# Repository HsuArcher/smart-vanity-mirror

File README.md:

# smart-vanity-mirror

Custom built ESP8266 based smart vanity mirror with touch controls, USB-C power and programming integration, custom CADed frame and custom PCB.

## Features

- Adustable LEDs brightness and color
- Touch Sensor Controls
- Custom Built Housing
- USB C Port for Power and Programming

## Hardware Overview

What this shows:
USB-C Programmer and Power Supply, Voltage Regulation, ESP8266 Microcontroller, Touch Input Circuit, LED Output Stage

### USB-C and USB to Serial Port

The system is powered and programmed through a USB-C connector supplying 5 V and a CH340C USB to Serial UART converter.

Key design elements:
- VBUS provides 5 V input.
- CC resistors are used to negotiate default USB power mode.
- The CH340C communicates with the ESP8266 when the USB C is connected to a computer. 
- GPIO 0 boot mode circuitry and Reset circuitry
- A polyfuse is used as overcurrent protection.

### Voltage Regulation

The ESP8266 operates at 3.3 V, so a voltage regulator steps down 5 V from USB-C to 3.3 V.

Key design elements:
- 5V to 3.3V Buck Converter

### ESP8266 Microcontroller

The ESP8266 serves as the main controller for, handling touch input, driving LED outputs, and managing firmware logic

Key design elements:
- Proper decoupling capacitors near VCC
- EN (enable) pull-up resistor
- Manual Reset Switch

### Touch Input Circuit

The FDC1004-Q1 is a 4-Channel Capacitance-to-Digital Converter which is used to detect when the user touches metal pads. This data is sent to the ESP8266 to control the lights

<!-- Future Improvements

Facial recognition lighting presets

Mobile app control

Ambient light auto-adjustment

Bluetooth speaker integration -->

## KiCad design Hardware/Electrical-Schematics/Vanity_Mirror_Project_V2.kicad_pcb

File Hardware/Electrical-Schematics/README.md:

# Schematics
KiCAD schematics files and PDFs

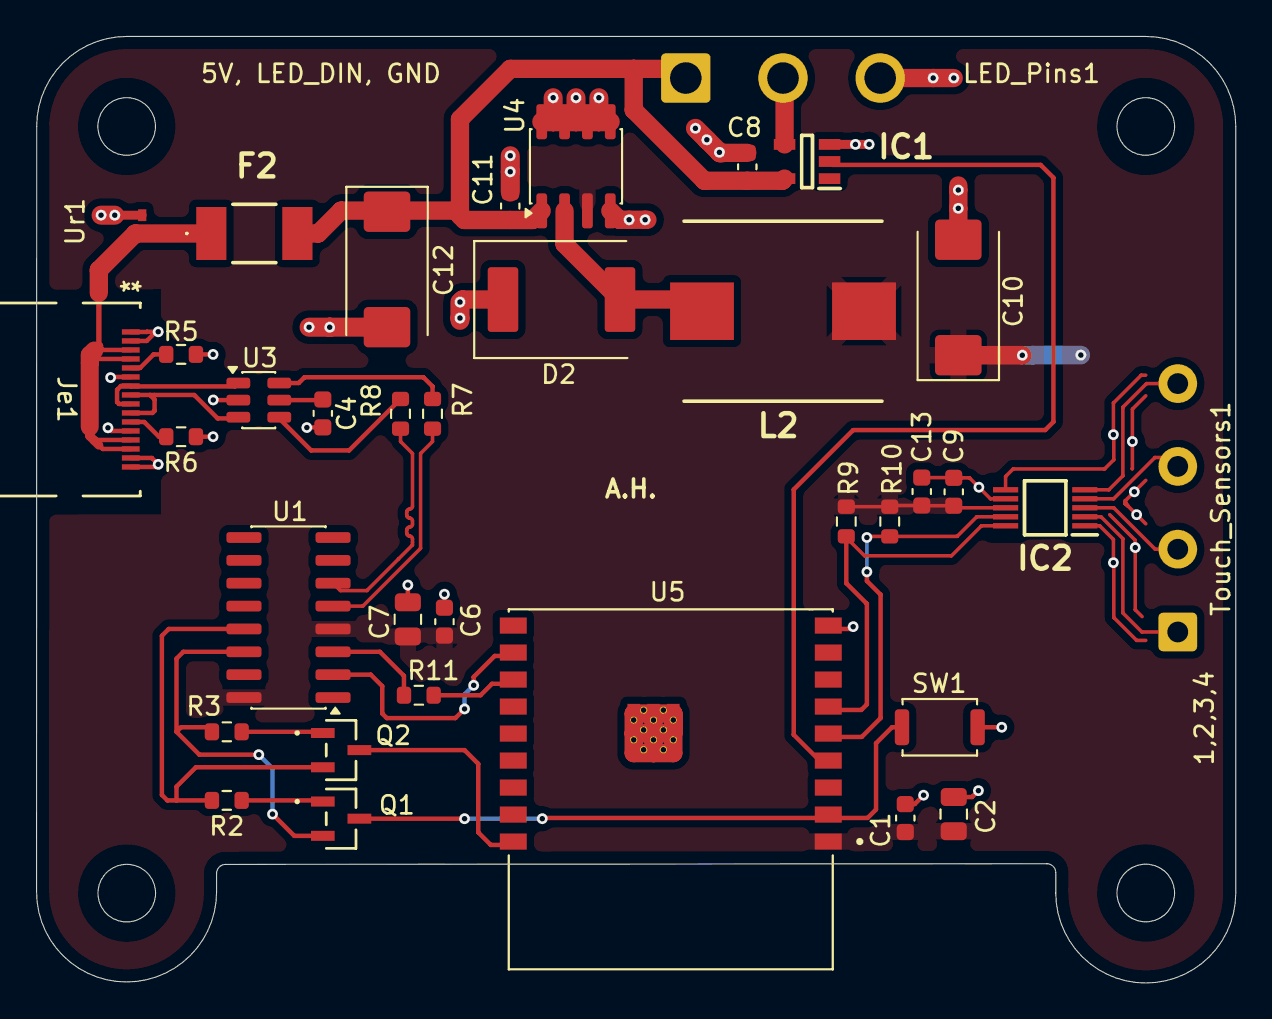
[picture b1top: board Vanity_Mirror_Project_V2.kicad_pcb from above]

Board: 2 copper layers, 66.6 x 52.6 mm, 40 parts (0 on the bottom side), 30 nets.

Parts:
C1, C4, C6, C8, C9: 0.1uF; C_0603_1608Metric
C2, C7: 10uF; C_0805_2012Metric
C10: 330uF; CP_EIA-7343-31_Kemet-D_HandSolder
C11, C13: 1uF; C_0603_1608Metric
C12: 470uF; CP_EIA-7343-31_Kemet-D_HandSolder
D2: Diode; P27_DO-214AB_SMC
F2: MF-MSMF300_6X-2; MFMSMF3006X2
H1, H2, H3, H4: MountingHole; MountingHole_3.2mm_M3
IC1: SN74LV1T34QDBVRQ1; SOT95P280X145-5N
IC2: FDC1004QDGSRQ1; SOP50P490X110-10N
Je1: 10155435-00011LF-Custom; 2130830005_MOL
L2: 22uH; INDPM110100X400N
LED_Pins1: Conn_01x03_Pin; SolderWire-1sqmm_1x03_P5.4mm_D1.4mm_OD2.7mm
Q1, Q2: Q_NPN_BEC; SOT-23-3_1P4X3P040_ONS
R2, R3: 12k; R_0603_1608Metric
R5, R6: 5.1k; R_0603_1608Metric
R7, R8: 27; R_0603_1608Metric
R9, R10: 4.7k; R_0603_1608Metric
R11: 499; R_0603_1608Metric
SW1: RST; SW_Push_SPST_NO_Alps_SKRK
Touch_Sensors1: Conn_01x04_Pin; SolderWire-0.5sqmm_1x04_P4.6mm_D0.9mm_OD2.1mm
U1: CH340C; SOIC-16_3.9x9.9mm_P1.27mm
U3: USBLC6-2SC6; SOT-23-6
U4: XL1509-3.3; SOIC-8_3.9x4.9mm_P1.27mm
U5: ESP32-C3-WROOM-02-N4; MODULE_ESP32-C3-WROOM-02-H4
Ur1: CPDQR5V0U; CPDQR

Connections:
+3.3V: C1.1, C2.1, C6.1, C7.1, C9.1, C10.1, C13.1, IC2.8 (VDD), L2.2, R9.2, R10.2, U1.4 (V3), U1.16 (VCC), U4.3 (FB), U5.1 (3V3)
+5V: C8.1, C11.1, C12.1, F2.2, IC1.5 (VCC), LED_Pins1.1, U4.1 (VIN)
/D+: R7.1, U1.5 (UD+)
/D-: R8.1, U1.6 (UD-)
/EN: Q1.3 (C), SW1.2, U5.2 (EN)
/GPIO0: Q2.3 (C), U5.18 (IO0)
/LED_DIN: IC1.4 (Y), LED_Pins1.2
/RX: U1.2 (TXD), U5.11 (RXD)
/SCL: IC2.9 (SCL), R10.1, U5.5 (IO6)
/SDA: IC2.10 (SDA), R9.1, U5.6 (IO7)
/SN74_1A: IC1.2 (A), U5.4 (IO5)
/TX: R11.2, U1.3 (RXD)
GND: C1.2, C2.2, C4.2, C6.2, C7.2, C8.2, C9.2, C10.2, C11.2, C12.2, C13.2, D2.1 (A), IC1.3 (GND), IC2.1 (SHLD1), IC2.6 (SHLD2), IC2.7 (GND), Je1.A1 (GND), Je1.A8 (SBU1), Je1.A12 (GND), Je1.B1 (GND), Je1.B8 (SBU2), Je1.B12 (GND), LED_Pins1.3, R5.1, R6.1, SW1.1, U1.1 (GND), U3.2 (GND), U4.4 (~EN), U4.5 (GND), U4.6 (GND), U4.7 (GND), U4.8 (GND), U5.9 (GND), U5.19 (GND__1), U5.20 (GND__2), U5.21 (GND__3), U5.22 (GND__4), U5.23 (GND__5), U5.24 (GND__6), U5.25 (GND__7), U5.26 (GND__8), U5.27 (GND__9), U5.28 (GND__10), U5.29 (GND__11), U5.30 (GND__12), U5.31 (GND__13), U5.32 (GND__14), U5.33 (GND__15), U5.34 (GND__16), U5.35 (GND__17), U5.36 (GND__18), U5.37 (GND__19), U5.38 (GND__20), U5.39 (GND__21), Ur1.2
unnamed: D2.2 (C), L2.1, U4.2 (OUT)
unnamed: IC2.2 (CIN1), Touch_Sensors1.1
unnamed: IC2.3 (CIN2), Touch_Sensors1.2
unnamed: IC2.4 (CIN3), Touch_Sensors1.3
unnamed: IC2.5 (CIN4), Touch_Sensors1.4
unnamed: Je1.A5 (CC1), R5.2
unnamed: Je1.B5 (CC2), R6.2
unnamed: Je1.A6 (D+), Je1.B6 (D+), U3.1 (I/O1)
unnamed: Je1.A7 (D-), Je1.B7 (D-), U3.3 (I/O2)
unnamed: Q1.1 (B), R2.1
unnamed: Q1.2 (E), R3.2, U1.14 (~RTS)
unnamed: Q2.1 (B), R3.1
unnamed: Q2.2 (E), R2.2, U1.13 (~DTR)
unnamed: R7.2, U3.6 (I/O1)
unnamed: R8.2, U3.4 (I/O2)
unnamed: C4.1, F2.1, Je1.A4 (VBUS), Je1.A9 (VBUS), Je1.B4 (VBUS), Je1.B9 (VBUS), U3.5 (VBUS), Ur1.1
unnamed: R11.1, U5.12 (TXD)

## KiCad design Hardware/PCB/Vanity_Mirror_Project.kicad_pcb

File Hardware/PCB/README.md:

# PCB 
KiCAD PCB layout and footprints and symbols used.

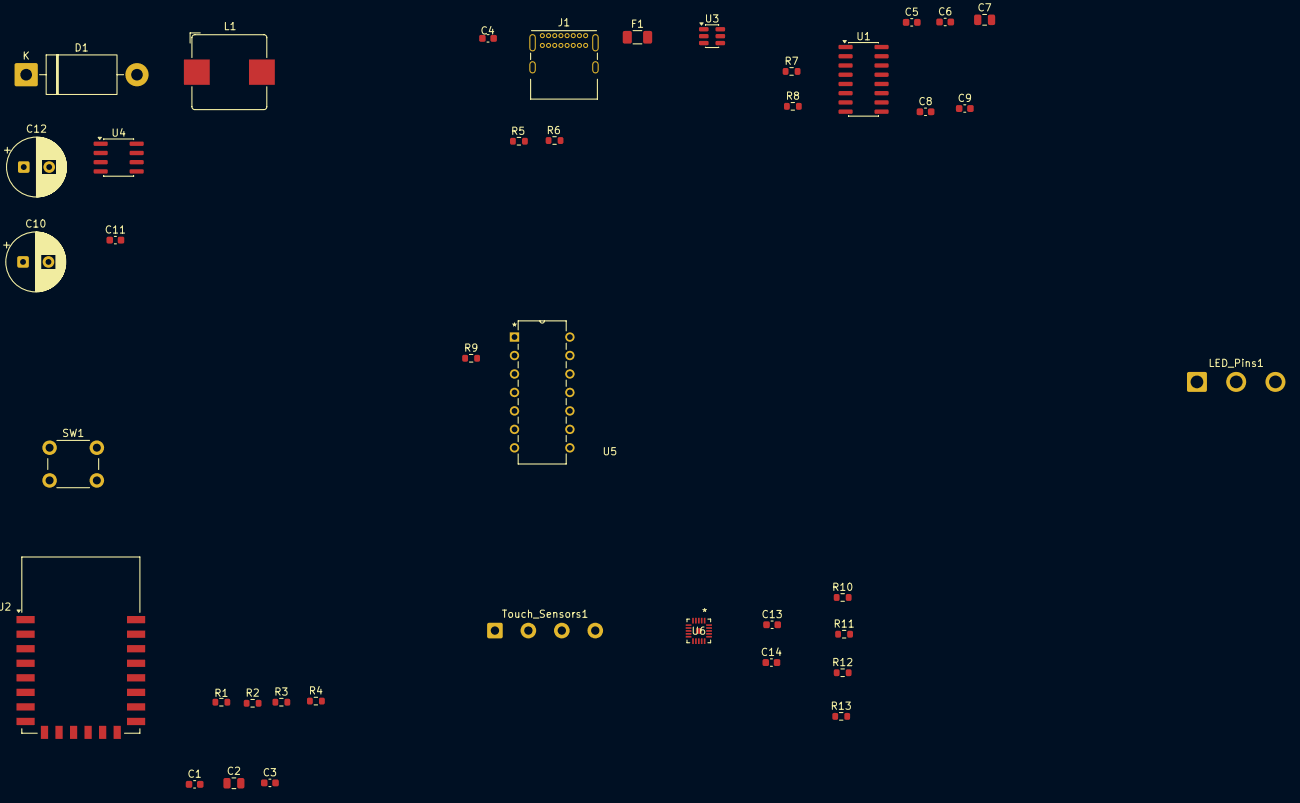
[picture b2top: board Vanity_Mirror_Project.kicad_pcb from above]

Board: 2 copper layers, 40 parts (0 on the bottom side), 33 nets, no tracks yet.

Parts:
C1, C3, C4, C5, C6, C8, C9, C13, C14: 0.1uF; C_0603_1608Metric
C2, C7: 10uF; C_0805_2012Metric
C10, C12: 470uF; CP_Radial_D8.0mm_P3.50mm
C11: 1uF; C_0603_1608Metric
D1: 1N5820; D_DO-201AD_P15.24mm_Horizontal
F1: Polyfuse; Fuse_1206_3216Metric
J1: USB_C_Receptacle_USB2.0_14P; USB_C_Receptacle_GCT_USB4085
L1: 22uH; L_Bourns_SRP1038C_10.0x10.0mm
LED_Pins1: Conn_01x03_Pin; SolderWire-1sqmm_1x03_P5.4mm_D1.4mm_OD2.7mm
R1, R2, R3, R4, R11, R12, R13: 10k; R_0603_1608Metric
R5, R6: 5.1k; R_0603_1608Metric
R7, R8: 27; R_0603_1608Metric
R9: 330; R_0603_1608Metric
R10: 75k; R_0603_1608Metric
SW1: RST; SW_PUSH_6mm
Touch_Sensors1: Conn_01x04_Pin; SolderWire-0.5sqmm_1x04_P4.6mm_D0.9mm_OD2.1mm
U1: CH340C; SOIC-16_3.9x9.9mm_P1.27mm
U2: ESP-12F; ESP-12E
U3: USBLC6-2SC6; SOT-23-6
U4: XL1509-3.3; SOIC-8_3.9x4.9mm_P1.27mm
U5: SN74AHCT125N
U6: MPR121QR2; QFN20_FRE

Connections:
+3.3V: C1.1, C2.1, C6.1, C7.1, C10.1, C13.1, L1.2, R1.2, R2.2, R3.2, R4.1, R11.2, R12.2, R13.2, U1.16 (VCC), U2.8 (VCC), U4.3 (FB), U6.20 (VDD)
+5V: C4.1, C11.1, C12.1, F1.1, F1.2, J1.A4 (VBUS), J1.A9 (VBUS), J1.B4 (VBUS), J1.B9 (VBUS), LED_Pins1.1, U3.5 (VBUS), U4.1 (VIN), U5.14 (VCC)
/LED_DIN: LED_Pins1.2, U5.3 (1Y)
/RX: U1.2 (TXD), U2.21 (GPIO3/RXD)
/SCL: R11.1, U2.20 (GPIO5), U6.2 (SCL)
/SDA: R12.1, U2.6 (GPIO12), U6.3 (SDA)
/SN74_1A: R9.2, U2.19 (GPIO4)
/TX: U1.3 (RXD), U2.22 (GPIO1/TXD)
/~DTR: C8.2, R2.1, U2.3 (EN)
/~IRQ: R13.1, U2.7 (GPIO13), U6.1 (*IRQ)
/~RTS: C9.2, R3.1, U2.18 (GPIO0)
GND: C1.2, C2.2, C3.2, C4.2, C5.2, C6.2, C7.2, C10.2, C11.2, C12.2, C13.2, C14.2, D1.2 (A), J1.A1 (GND), J1.A12 (GND), J1.B1 (GND), J1.B12 (GND), J1.S1 (SHIELD), LED_Pins1.3, R5.1, R6.1, R10.1, SW1.1, U1.1 (GND), U2.15 (GND), U2.16 (GPIO15), U3.2 (GND), U4.4 (~EN), U4.5 (GND), U4.6 (GND), U4.7 (GND), U4.8 (GND), U5.1 (*1OE), U5.7 (GND), U6.4 (ADDR), U6.6 (VSS)
unnamed: D1.1 (K), L1.1, U4.2 (OUT)
unnamed: J1.A5 (CC1), R5.2
unnamed: J1.B5 (CC2), R6.2
unnamed: J1.A6 (D+), J1.B6 (D+), U3.1 (I/O1)
unnamed: J1.A7 (D-), J1.B7 (D-), U3.3 (I/O2)
unnamed: R7.2, U3.6 (I/O1)
unnamed: R8.2, U3.4 (I/O2)
unnamed: Touch_Sensors1.1, U6.8 (ELE0)
unnamed: Touch_Sensors1.2, U6.9 (ELE1)
unnamed: Touch_Sensors1.3, U6.10 (ELE2)
unnamed: Touch_Sensors1.4, U6.11 (ELE3)
unnamed: R7.1, U1.5 (UD+)
unnamed: R8.1, U1.6 (UD-)
unnamed: C5.1, U1.4 (V3)
unnamed: C8.1, U1.13 (~DTR)
unnamed: C9.1, U1.14 (~RTS)
unnamed: R4.2, U2.17 (GPIO2)
unnamed: C3.1, R1.1, SW1.2, U2.1 (~RST)
unnamed: R9.1, U5.2 (1A)
unnamed: R10.2, U6.7 (REXT)
unnamed: C14.1, U6.5 (VREG)

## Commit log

2026-01-27 Create Revisions.md
    description for the initial design at the time of creating the repo
2026-01-29 Initial status of the mirror
    committing all the designs, design decisions, and schematics of the project so far
2026-01-30 Cleaning up the REPO
    moving the gitignore file to the main git folder
2026-02-09 PCB Design Progress
    Made progress with the PCB design and reorganized the gitignores so that it works.
2026-03-05 Initial PCB layout and Schematic Revisions
    Revised some wiring in the schematic and fixed some wiring mistakes. Created an initial layout for the PCB
2026-03-10 1st PCB design
    Finished the routing of the PCB and added BJTs for auto programming and auto resetting.
2026-03-10 Updating the README on front page
2026-03-10 Updating front page README
    second push due to file error
2026-03-10 Updating front page README
    added .svg file for the picture on the front page and changed the README to display it
2026-03-24 updating the version
    changing laptops so pushing the minor changes made so that the new laptop has the most recent version
2026-04-07 Cleaning files
    Switching Kicad versions and switching laptops
2026-04-27 2nd version of the design
    Changed multiple footprints to smd parts, Made a 2nd version for the PCB utilizing a power plane. PCB is ready to be manufactured
